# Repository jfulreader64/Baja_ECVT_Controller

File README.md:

# Baja_ECVT_Controller
ECVT Controller for brushed motor, 15a Sustained Current

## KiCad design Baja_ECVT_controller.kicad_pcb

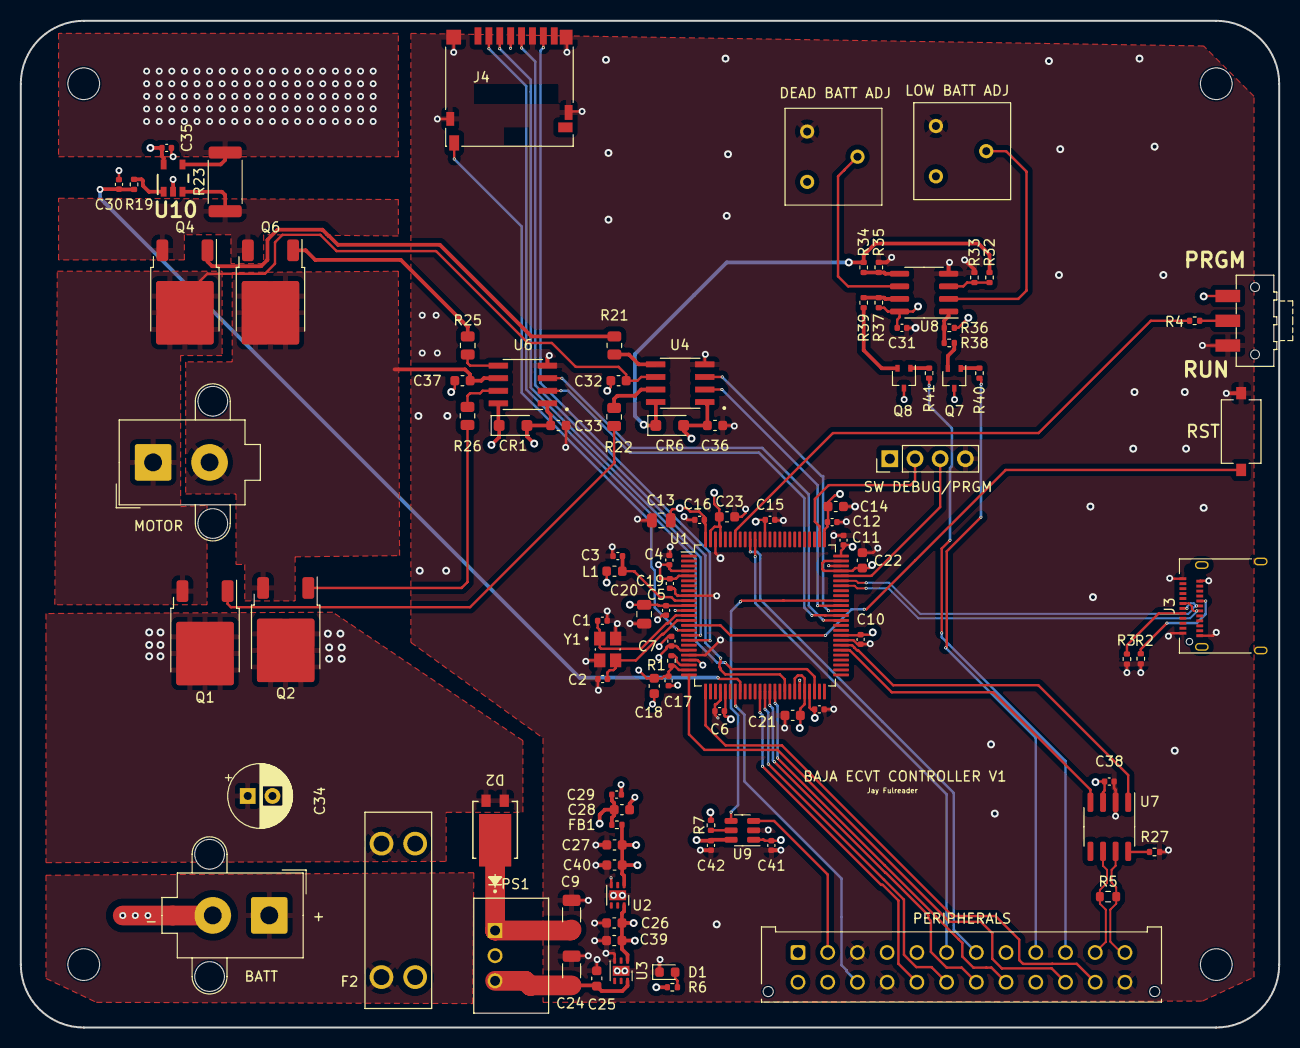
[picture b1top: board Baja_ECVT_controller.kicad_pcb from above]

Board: 4 copper layers, 127.0 x 101.6 mm, 105 parts (0 on the bottom side), 75 nets.

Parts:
C1, C2: 8pF; C_0402_1005Metric
C3: 220p; C_0402_1005Metric
C4, C5, C6, C7, C8, C10, C11, C12, C15, C16, C17, C19, C31, C35, C38, C41, C42: 100n; C_0402_1005Metric
C9: 10u; C_1206_3216Metric
C13, C20: 4.7u; C_0805_2012Metric
C14, C18, C25, C26, C27, C28, C32, C33, C36, C37, C39, C40: 1u; C_0603_1608Metric
C21, C22, C23: 2.2u; C_0603_1608Metric
C24: 22u; C_1206_3216Metric
C29: 10n; C_0402_1005Metric
C30: 1n; C_0402_1005Metric
C34: 47u; CP_Radial_D6.3mm_P2.50mm
CR1, CR6: DSS110U; D_SOD-123F
D1: LED; LED_0603_1608Metric
D2: D_Schottky_KAA; TO-277B_MBR1560S_SME
F2: 3557-2; FUSE_3557-2
FB1: 120R; R_0402_1005Metric
H1, H2, H3, H4: MountingHole; MountingHole_3.2mm_M3
J1: Conn_01x04_Pin; PinHeader_1x04_P2.54mm_Vertical
J2, J5: Conn_01x02_Pin; Molex_Mega-Fit_76829-0002_2x01_P5.70mm_Vertical
J3: USB_C_Receptacle_USB2.0; USB_C_Receptacle_Amphenol_12401610E4-2A
J4: Micro_SD_Card_Det2; microSD_HC_Hirose_DM3D-SF
J7: Conn_01x24_Pin; Molex_Micro-Fit_3.0_43045-2412_2x12_P3.00mm_Vertical
L1: 2.2u; L_0603_1608Metric
NT1: NetTie_2; NetTie-2_SMD_Pad2.0mm
PS1: LMP78_12-1.0R; CONV_K7803-500R3
Q1, Q2, Q4, Q6: NMOS; TO-252-2
Q7, Q8: PMOS; SOT-323_SC-70
R1: 47; R_0402_1005Metric
R2, R3: 5k1; R_0402_1005Metric
R4, R7, R27, R33, R35: 10k; R_0402_1005Metric
R5: 120; R_0603_1608Metric
R6, R19: 1k; R_0402_1005Metric
R21, R22, R25, R26: 100; R_0805_2012Metric
R23: 1m; R_2512_6332Metric
R32, R34: 100k; R_0402_1005Metric
R36, R37: 2k2; R_0402_1005Metric
R38, R39: 100; R_0402_1005Metric
R40, R41: 220; R_0402_1005Metric
RV1, RV2: 10k; Potentiometer_Bourns_3386F_Vertical
SW1: SW_Push; SW_Tactile_SPST_NO_Straight_CK_PTS636Sx25SMTRLFS
SW2: SW_SPDT; SW_SPDT_CK-JS102011SAQN
U1: STM32H725VGT6; LQFP-100_14x14mm_P0.5mm
U2: AP7370-33FDC; DFN-6-1EP_2x2mm_P0.65mm_EP1.01x1.7mm
U3: AP7370-50FDC; DFN-6-1EP_2x2mm_P0.65mm_EP1.01x1.7mm
U4, U6: IR2103STRPBF; SOIC127P600X175-8N
U7: SN65HVD230; SOIC-8_3.9x4.9mm_P1.27mm
U8: LM393; SOIC-8_3.9x4.9mm_P1.27mm
U9: SN74LVC1T45DBV; SOT-23-6
U10: INA180A2IDBVR; DBV0005A_N
Y1: TSX-3225_16.0000MF09Z-AC6; XTAL_TSX-3225_16.0000MF09Z-AC6

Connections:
+2V5: C21.1, C22.1, C23.1, L1.1, U1.12 (VFBSMPS), U1.44 (VCAP), U1.46 (VDDLDO), U1.72 (VCAP), U1.74 (VDDLDO), U1.97 (VCAP), U1.99 (VDDLDO)
+3.3V: C4.1, C5.1, C6.1, C7.1, C8.1, C10.1, C11.1, C12.1, C13.1, C14.1, C15.1, C16.1, C19.1, C20.1, C27.1, C38.1, C40.1, C42.2, FB1.2, J1.1, J4.4 (VDD), J7.14, SW2.3 (C), U1.4 (VDD), U1.5 (VBAT), U1.11 (VDDSMPS), U1.20 (VDD), U1.30 (VDD), U1.47 (VDD), U1.59 (VDD), U1.75 (VDD), U1.76 (VDD33USB), U1.88 (VDD), U1.100 (VDD), U2.1 (VO), U7.3 (VCC), U9.6 (VCCB)
+5V: C26.1, C31.1, C39.1, C41.1, J7.1, J7.5, J7.21, Q7.3 (S), Q8.3 (S), R6.1, R7.2, R36.1, R37.1, RV1.1, RV2.1, U2.6 (VI), U3.1 (VO), U8.8 (V+), U9.1 (VCCA)
+12V: C24.1, C25.1, C33.1, C36.1, CR1.2, CR6.2, PS1.3 (+VO), U3.6 (VI), U4.1 (VCC), U6.1 (VCC)
+BATT: F2.1_1, J2.1
/BOOT0: R4.1, U1.94 (BOOT0)
/Hall_effect_3.3v: U1.66 (PA8), U9.4 (B)
/NRST: SW1.2, U1.15 (NRST)
/OSC_IN: C1.2, U1.13 (PH0-OSC_IN), Y1.1
/OSC_OUT: C2.1, U1.14 (PH1-OSC_OUT), Y1.3
/SWCLK: J1.2, U1.77 (PA14)
/SWDIO: J1.3, U1.71 (PA13)
/USB_D+: J3.A6 (D+), J3.B6 (D+), U1.70 (PA12)
/USB_D-: J3.A7 (D-), J3.B7 (D-), U1.69 (PA11)
CAN_+: J7.12, R5.2, U7.7 (CANH)
CAN_-: J7.11, R5.1, U7.6 (CANL)
CAN_RX: U1.56 (PD12), U7.4 (R)
CAN_TX: U1.57 (PD13), U7.1 (D)
Clutch_Button: J7.15, U1.32 (PA5)
Current_sense_1: C30.1, R19.1, U1.33 (PA6)
Dead_Batt_ind: J7.10, R41.2
Encoder1_1: J7.6, U1.90 (PB4)
Encoder1_2: J7.7, U1.91 (PB5)
Encoder2_1: J7.22, U1.25 (PA0)
Encoder2_2: J7.23, U1.26 (PA1)
GND: C1.1, C2.2, C3.1, C4.2, C5.2, C6.2, C7.2, C8.2, C9.2, C10.2, C11.2, C12.2, C13.2, C14.2, C15.2, C16.2, C19.2, C20.2, C21.2, C22.2, C23.2, C24.2, C25.2, C26.2, C27.2, C31.2, C33.2, C34.2, C36.2, C38.2, C39.2, C40.2, C41.2, C42.1, D1.1 (K), J1.4, J2.2, J3.A1 (GND), J3.A12 (GND), J3.B1 (GND), J3.B12 (GND), J4.6 (VSS), J4.11 (SHIELD), J7.3, J7.8, J7.16, J7.24, NT1.2, PS1.2 (GND), R2.2, R3.2, R23.2, R27.2, R33.2, R35.2, RV1.3, RV2.3, SW1.1, SW2.1 (A), U1.9 (VSSSMPS), U1.21 (VSS), U1.29 (VSS), U1.45 (VSS), U1.58 (VSS), U1.73 (VSS), U1.98 (VSS), U2.3 (GND), U2.7 (GND), U3.3 (GND), U3.7 (GND), U4.4 (COM), U6.4 (COM), U7.2 (GND), U8.4 (V-), U9.2 (GND), U10.4 (IN-), Y1.2 (GND), Y1.4 (GND)
GNDA: C17.2, C18.2, C28.2, C29.2, C30.2, C35.2, NT1.1, U1.22 (VSSA), U10.2 (GND)
GPIO_1: J7.17, U1.37 (PB0)
GPIO_2: J7.18, U1.38 (PB1)
GPIO_3: J7.19, U1.39 (PB2)
GPIO_4: J7.20, U1.40 (PE7)
HIN_1: U1.65 (PC9), U4.2 (HIN)
HIN_2: U1.63 (PC7), U6.2 (HIN)
Hall_Effect: J7.2, U9.3 (A)
Low_Batt_ind: J7.9, R40.2
Motor_A: C32.2, J5.1, Q1.3 (S), Q4.2 (D), U4.6 (VS)
Motor_B: C37.2, J5.2, Q2.3 (S), Q6.2 (D), U6.6 (VS)
unnamed: D1.2 (A), R6.2
unnamed: C9.1, D2.1 (K), PS1.1 (VIN)
unnamed: J3.A5 (CC1), R3.1
unnamed: J3.B5 (CC2), R2.1
unnamed: Q1.1 (G), R22.2
unnamed: Q2.1 (G), R26.1
unnamed: Q4.1 (G), R21.2
unnamed: Q4.3 (S), Q6.3 (S), R23.1, U10.3 (IN+)
unnamed: Q6.1 (G), R25.1
unnamed: Q7.1 (D), R40.1
unnamed: Q7.2 (G), R38.2
unnamed: Q8.1 (D), R41.1
unnamed: Q8.2 (G), R39.2
unnamed: R36.2, R38.1, U8.1
unnamed: R37.2, R39.1, U8.7
unnamed: R4.2, SW2.2 (B)
unnamed: C3.2, L1.2, U1.10 (VLXSMPS)
unnamed: R1.2, U1.23 (VREF+)
unnamed: R22.1, U4.7 (HO)
unnamed: R21.1, U4.5 (LO)
unnamed: R26.2, U6.7 (HO)
unnamed: R25.2, U6.5 (LO)
unnamed: R27.1, U7.8 (Rs)
unnamed: R32.2, R33.1, U8.3 (+)
unnamed: RV2.2, U8.2 (-)
unnamed: R34.2, R35.1, U8.5 (+)
unnamed: RV1.2, U8.6 (-)
unnamed: R7.1, U9.5 (DIR)
unnamed: R19.2, U10.1 (OUT)
SD_sense: J4.10 (DET_A), U1.16 (PC0)
SPI_MOSI: J4.3 (CMD), U1.17 (PC1)
SPI_MOSO: J4.7 (DAT0), U1.18 (PC2_C)
SPI_NSS: J4.2 (DAT3/CD), U1.48 (PB12)
SPI_SCK: J4.5 (CLK), U1.42 (PB10)
VDDA: C17.1, C18.1, C28.1, C29.1, C35.1, FB1.1, R1.1, U1.24 (VDDA), U10.5 (VS)
Vdrive: C32.1, C34.1, C37.1, CR1.1, CR6.1, D2.2 (A), D2.3 (A), F2.2_1, Q1.2 (D), Q2.2 (D), R32.1, R34.1, U4.8 (VB), U6.8 (VB)
nLIN_1: U1.64 (PC8), U4.3 (~LIN)
nLIN_2: U1.62 (PC6), U6.3 (~LIN)

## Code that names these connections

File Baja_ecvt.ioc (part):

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Mcu.Name=STM32H725VGTx
Mcu.Package=LQFP100
Mcu.UserName=STM32H725VGTx
PA0.Signal=S_TIM2_CH1_ETR
PA1.Signal=S_TIM2_CH2
PA11.Mode=Host_FS
PA11.Signal=USB_OTG_HS_DM
PA12.Mode=Host_FS
PA12.Signal=USB_OTG_HS_DP
PA13(JTMS/SWDIO).Mode=Serial_Wire
PA13(JTMS/SWDIO).Signal=DEBUG_JTMS-SWDIO
PA14(JTCK/SWCLK).Mode=Serial_Wire
PA14(JTCK/SWCLK).Signal=DEBUG_JTCK-SWCLK
PA5.GPIOParameters=GPIO_PuPd
PA5.GPIO_PuPd=GPIO_PULLUP
PA5.Signal=GPIO_Input
PA6.Signal=ADCx_INP3
PA8.Signal=S_TIM1_CH1
PB0.Signal=GPIO_Input
PB1.Signal=GPIO_Input
PB10.GPIOParameters=GPIO_PuPd
PB10.GPIO_PuPd=GPIO_PULLUP
PB10.Mode=Full_Duplex_Master
PB10.Signal=SPI2_SCK
PB12.GPIOParameters=GPIO_PuPd
PB12.GPIO_PuPd=GPIO_PULLUP
PB12.Mode=NSS_Signal_Hard_Input
PB12.Signal=SPI2_NSS
PB2.Signal=GPIO_Input
PB4(NJTRST).Signal=S_TIM3_CH1
PB5.Signal=S_TIM3_CH2
PC0.Signal=GPIO_Input
PC1.GPIOParameters=GPIO_PuPd
PC1.GPIO_PuPd=GPIO_PULLUP
PC1.Mode=Full_Duplex_Master
PC1.Signal=SPI2_MOSI
PC2_C.Mode=Full_Duplex_Master
PC2_C.Signal=SPI2_MISO
PC4.Signal=ADCx_INP4
PC6.Signal=S_TIM8_CH1
PC7.Signal=S_TIM8_CH2
PC8.Signal=S_TIM8_CH3
PC9.Signal=S_TIM8_CH4
PD12.Mode=FDCAN_Activate
PD12.Signal=FDCAN3_RX
PD13.Mode=FDCAN_Activate
PD13.Signal=FDCAN3_TX
PE7.Signal=GPIO_Input
PH0-OSC_IN.Mode=HSE-External-Oscillator
PH0-OSC_IN.Signal=RCC_OSC_IN
PH1-OSC_OUT.Mode=HSE-External-Oscillator
PH1-OSC_OUT.Signal=RCC_OSC_OUT
RCC.HSE_VALUE=16000000
RCC.SYSCLKFreq_VALUE=64000000
board=custom
